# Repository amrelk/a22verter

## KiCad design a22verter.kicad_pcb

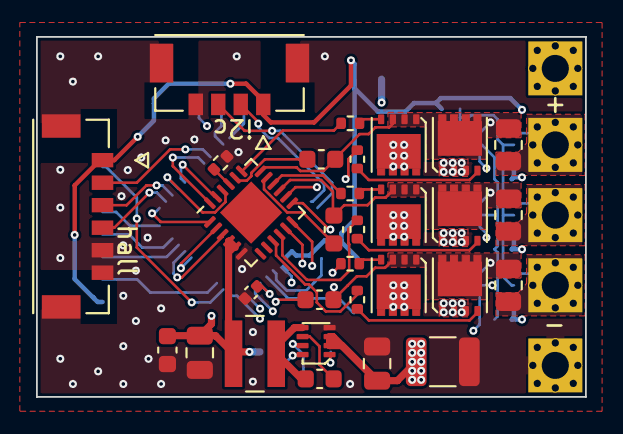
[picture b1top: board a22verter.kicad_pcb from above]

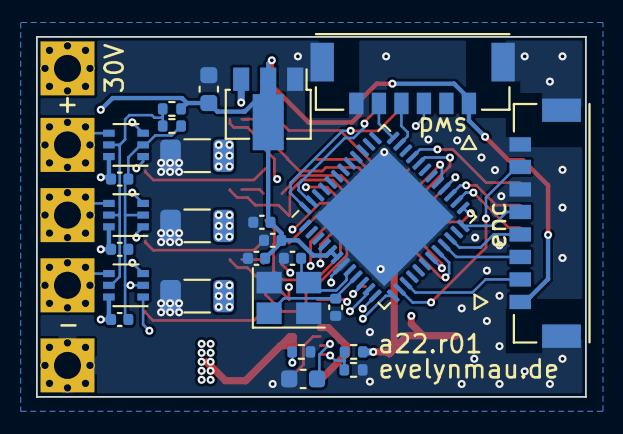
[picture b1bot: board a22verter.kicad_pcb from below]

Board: 4 copper layers, 30.5 x 20.0 mm, 62 parts (27 on the bottom side), 57 nets.

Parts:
C1, C15, C19, C20, C21: 100n; C_0402_1005Metric
C2: 1u; C_0402_1005Metric
C3: 10u; C_0402_1005Metric
C4, C5: 16p; C_0402_1005Metric
C12, C13, C14, C27: 100n; C_0603_1608Metric
C16, C17, C18: 1u; C_1206_3216Metric
C22, C23: 10u; C_0603_1608Metric
C24: 10u; C_1210_3225Metric
C25: 100n; C_0805_2012Metric
C26: 33n; C_0603_1608Metric
C28: 47u; C_0805_2012Metric
J1: IN+; SolderPad
J2: IN-; SolderPad
J3: swd; MOLEX_5055670651
J4: U; SolderPad
J5: V; SolderPad
J6: W; SolderPad
J9: i2c; MOLEX_5055670451
J10: enc; MOLEX_5055670851
J11: hall; MOLEX_5055670651
L1: 6.8u; L_Wuerth_MAPI-4030
NT1: NetTie_2; NetTie-2_SMD_Pad0.5mm
Q1, Q2, Q3, Q4, Q5, Q6: AON7418; DFN3.3x3.3-EP
R1: 0; R_0402_1005Metric
R2, R3, R4, R5, R6, R7: 16; R_0402_1005Metric
R8, R9, R10: 1m; R_0805_2012Metric
R11, R12, R15: 10k; R_0402_1005Metric
R13: 22k; R_0402_1005Metric
R14: 140k; R_0402_1005Metric
U1: STM32G071CBU3; QFN-48-1EP_7x7mm_P0.5mm_EP5.45x5.45mm
U2: DRV8300DRGE; VQFN-24-1EP_4x4mm_P0.5mm_EP2.45x2.45mm
U3, U4, U5: INA186; SOT-363_SC-70-6
U6: AP1117-33; SOT-89-3
U7: TPS62933; SOT-583
Y1: RH100-8; Crystal_SMD_3225-4Pin_3.2x2.5mm

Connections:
+3V3: C1.1, C2.1, C3.2, C19.1, C20.1, C21.1, C23.1, J3.1, J9.1, J10.1, J11.1, R11.2, U1.5 (VREF+), U1.6 (VDD), U3.6 (V+), U4.6 (V+), U5.6 (V+), U6.2 (VO)
+12V: C22.1, C28.1, L1.2, R14.1, U2.4 (GVDD), U2.5 (MODE), U6.3 (VI)
/drive/sense_vref: R11.1, R12.2, U3.5 (REF), U4.5 (REF), U5.5 (REF)
/drive/u_sense_line: C12.2, Q1.1 (S), Q2.3 (D), R8.2, U2.18 (SHA), U3.3 (+)
/drive/u_sense_load: J4.1, R8.1, U3.4 (-)
/drive/v_sense_line: C13.2, Q3.1 (S), Q4.3 (D), R9.2, U2.15 (SHB), U4.3 (+)
/drive/v_sense_load: J5.1, R9.1, U4.4 (-)
/drive/w_sense_line: C14.2, Q5.1 (S), Q6.3 (D), R10.2, U2.12 (SHC), U5.3 (+)
/drive/w_sense_load: J6.1, R10.1, U5.4 (-)
/mcu/adc1_in0: U1.11 (PA0), U3.1
/mcu/adc1_in1: U1.12 (PA1), U4.1
/mcu/adc1_in2: U1.13 (PA2), U5.1
/mcu/adc1_in3: J10.7, U1.14 (PA3)
/mcu/hall_a: J11.2, U1.33 (PA11PA9)
/mcu/hall_b: J11.3, U1.27 (PB15)
/mcu/hall_c: J11.4, U1.26 (PB14)
/mcu/i2c1_scl: J9.2, U1.47 (PB8)
/mcu/i2c1_sda: J9.3, U1.48 (PB9)
/mcu/nrst: C15.1, J3.3, U1.10 (PF2-NRST)
/mcu/spi2_cipo: J10.3, U1.21 (PB2)
/mcu/spi2_copi: J10.2, U1.15 (PA4)
/mcu/spi2_cs: J10.5, U1.24 (PB12)
/mcu/spi2_sck: J10.4, U1.22 (PB10)
/mcu/swclk: J3.5, U1.36 (PA14-BOOT0)
/mcu/swdio: J3.4, U1.35 (PA13)
/mcu/tim1_ch1: U1.28 (PA8), U2.22 (INHA)
/mcu/tim1_ch1n: U1.25 (PB13), U2.1 (INLA)
/mcu/tim1_ch2: U1.29 (PA9), U2.23 (INHB)
/mcu/tim1_ch2n: U1.19 (PB0), U2.2 (INLB)
/mcu/tim1_ch3: U1.32 (PA10), U2.24 (INHC)
/mcu/tim1_ch3n: U1.20 (PB1), U2.3 (INLC)
GND: C1.2, C2.2, C3.1, C4.2, C5.2, C15.2, C16.2, C17.2, C18.2, C22.2, C23.2, C24.2, C25.2, C26.1, C28.2, J2.1, J3.6, J3.MP (MountPin), J9.4, J9.MP (MountPin), J10.6, J10.8, J10.MP (MountPin), J11.5, J11.6, J11.MP (MountPin), NT1.1, Q2.1 (S), Q4.1 (S), Q6.1 (S), R1.1, R13.2, R15.2, U1.7 (VSS), U1.49 (EPAD), U2.6 (GND), U6.1 (GND), U7.4 (GND), Y1.2, Y1.4
GNDA: C19.2, C20.2, C21.2, NT1.2, R12.1, U3.2 (GND), U4.2 (GND), U5.2 (GND)
unnamed: C4.1, U1.8 (PF0-OSC_IN), Y1.3
unnamed: C5.1, U1.9 (PF1-OSC_OUT), Y1.1
unnamed: C12.1, U2.20 (BSTA)
unnamed: C13.1, U2.17 (BSTB)
unnamed: C14.1, U2.14 (BSTC)
unnamed: C26.2, U7.7 (SS)
unnamed: C27.1, U7.6 (BST)
unnamed: C27.2, L1.1, U7.5 (SW)
unnamed: Q1.2 (G), R2.2
unnamed: Q2.2 (G), R3.2
unnamed: Q3.2 (G), R4.2
unnamed: Q4.2 (G), R5.2
unnamed: Q5.2 (G), R6.2
unnamed: Q6.2 (G), R7.2
unnamed: R1.2, U2.21 (DT)
unnamed: R2.1, U2.19 (GHA)
unnamed: R3.1, U2.11 (GLA)
unnamed: R4.1, U2.16 (GHB)
unnamed: R5.1, U2.10 (GLB)
unnamed: R6.1, U2.13 (GHC)
unnamed: R7.1, U2.9 (GLC)
unnamed: R13.1, U7.1 (RT)
unnamed: R14.2, R15.1, U7.8 (FB)
VBUS: C16.1, C17.1, C18.1, C24.1, C25.1, J1.1, Q1.3 (D), Q3.3 (D), Q5.3 (D), U7.2 (EN), U7.3 (VIN)

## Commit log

2023-01-24 finally uploading this
